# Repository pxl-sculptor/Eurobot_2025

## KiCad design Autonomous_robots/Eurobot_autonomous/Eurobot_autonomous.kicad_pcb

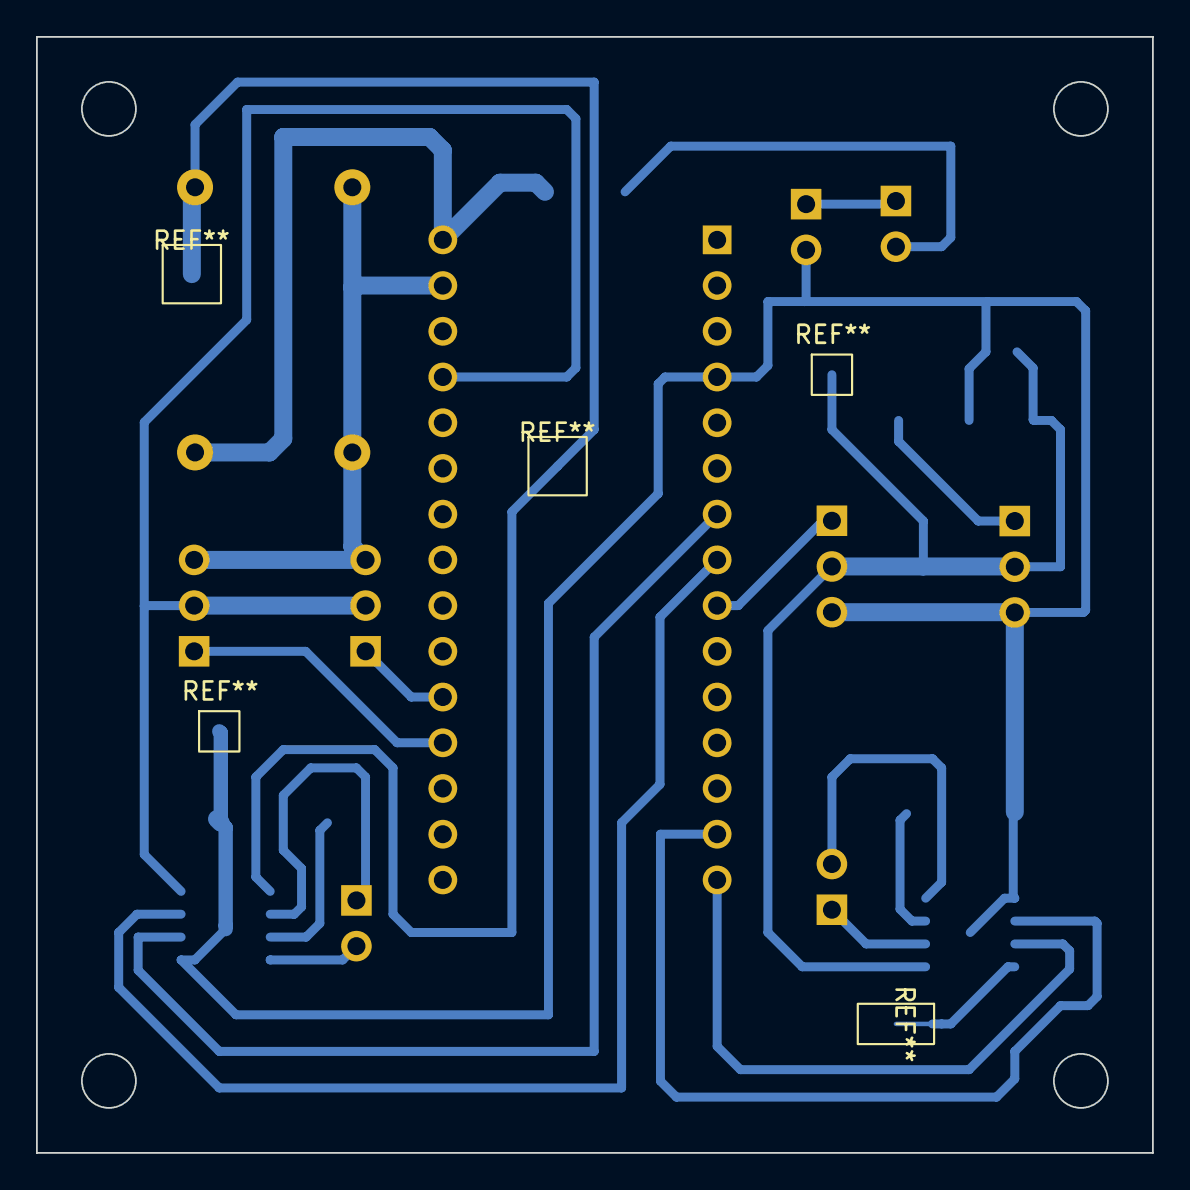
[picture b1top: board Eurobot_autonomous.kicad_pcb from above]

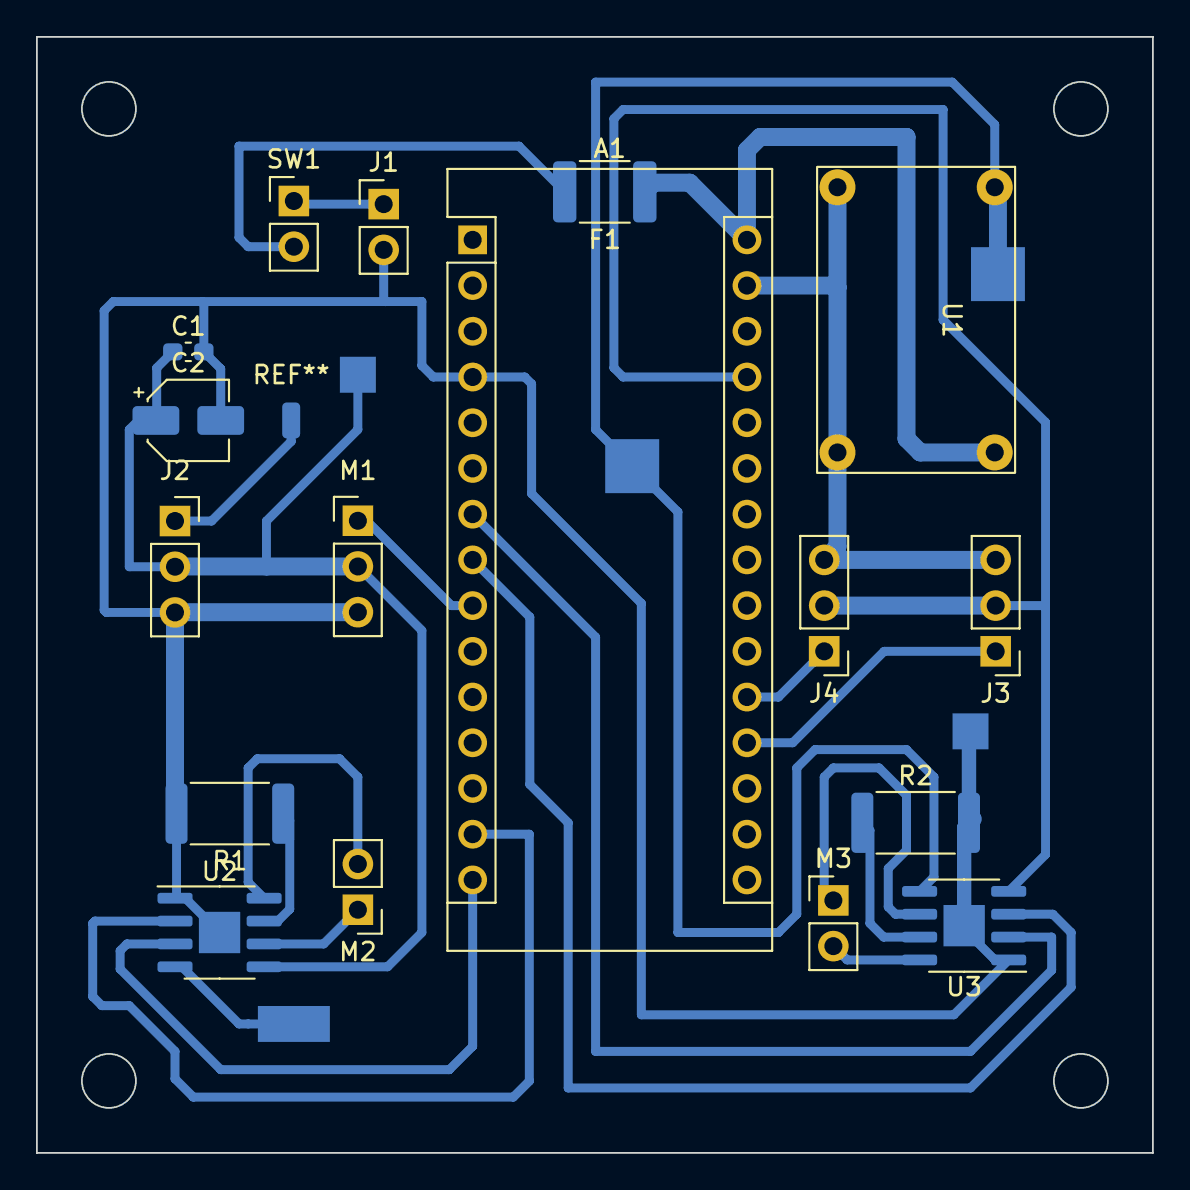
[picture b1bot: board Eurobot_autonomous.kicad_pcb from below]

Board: 2 copper layers, 62.0 x 62.0 mm, 17 parts (17 on the bottom side), 19 nets.

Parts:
A1: Arduino_Nano_v3.x; Arduino_Nano
C1: 0.1uf; C_0603_1608Metric_Pad1.08x0.95mm_HandSolder
C2: 47uf; CP_Elec_4x5.4
F1: Fuse; Fuse_1812_4532Metric_Pad1.30x3.40mm_HandSolder
J1: Conn_01x02; PinHeader_1x02_P2.54mm_Vertical
J2: Conn_01x03; PinSocket_1x03_P2.54mm_Vertical
J3, J4: Conn_01x03; PinHeader_1x03_P2.54mm_Vertical
M1: Motor_Servo; PinHeader_1x03_P2.54mm_Vertical
M2, M3: Motor_DC; PinHeader_1x02_P2.54mm_Vertical
R1, R2: 0.2R; R_2512_6332Metric
SW1: SW_DIP_x01; PinHeader_1x02_P2.54mm_Vertical
U1: dc-dc_converter; dc-dc_Mini
U2, U3: DRV8870DDA; HSOP-8-1EP_3.9x4.9mm_P1.27mm_EP2.3x2.3mm

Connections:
+5V: A1.27 (+5V), J3.2, J4.2, U2.4 (VREF), U3.4 (VREF)
+6V: C1.1, C2.1, J2.2, M1.2 (+), U1.1, U2.5 (VM), U3.5 (VM)
GNDD: A1.4 (GND), A1.29 (GND), C1.2, C2.2, J1.2, J2.3, J3.3, J4.3, M1.3 (-), R1.2, R2.2, U1.2, U1.3, U2.1 (GND), U2.9 (GND), U3.1 (GND), U3.9 (GND)
unnamed: A1.7 (D4), U3.2 (IN2)
unnamed: A1.8 (D5), U3.3 (IN1)
unnamed: A1.9 (D6), M1.1 (PWM)
unnamed: A1.19 (A0), J3.1
unnamed: A1.20 (A1), J4.1
unnamed: A1.30 (VIN), F1.1, J2.1, U1.4
unnamed: F1.2, SW1.2
unnamed: J1.1, SW1.1
unnamed: M2.1 (+), U2.6 (OUT1)
unnamed: M2.2 (-), U2.8 (OUT2)
unnamed: M3.1 (+), U3.6 (OUT1)
unnamed: M3.2 (-), U3.8 (OUT2)
unnamed: R1.1, U2.7 (ISEN)
unnamed: R2.1, U3.7 (ISEN)
unnamed: A1.14 (D11), U2.2 (IN2)
unnamed: A1.15 (D12), U2.3 (IN1)

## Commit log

2025-03-31 3d models added
2025-04-11 electronic circuit and printed circuit board added
2025-04-11 3D models of autonomous robots updated
2025-04-11 3D models of autonomous robots have been updated and files for CNC cutting in dxf format have been added
2025-04-11 added program code for esp32
2025-04-12 PCB for autonomous robots updated
2025-04-14 program for main robot updated, the ESP logic has been written
2025-04-15 program code for main robot updated, wheelbase logic written, sketch for gripper control added
2025-04-16 program for main robot updated, strafe is completely written
2025-04-17 updated program for main robot, completely written code for wheelbase
2025-05-02 program code updated
